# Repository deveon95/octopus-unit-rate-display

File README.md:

# Octopus Unit Rate Display for ESP32

This project gets JSON data from https://octopus.energy

The JSON data is parsed and used to get today's gas and electricity unit rates for the **Tracker** tariff and/or the current **Flexible** prices and/or the current **Agile** prices.

Prices are displayed on two or more 3-digit 7-segment displays to two decimal places if the unit rate is less than 10.00, or one decimal place if the unit rate is greater than or equal to 10.00. Values greater than or equal to 100.00 are displayed with no decimal places.

Negative prices are also supported. In such an event, the first digit will be used for the '-' character.

# Installation

You'll need to install esp-idf to build this project.

```
git clone https://github.com/deveon95/octopus-unit-rate-display
cd esp-idf-json/json-http-client2
chmod 777 getpem.sh
./getpem.sh
idf.py menuconfig
idf.py build flash monitor
```

The getpem.sh script gets the https certificate for octopus.energy. HTTPS is mandatory to use the Octopus API, and this step cannot be skipped! The script does work on Windows as well as Linux; you can run the script with Windows Subsystem for Linux, and you may already be able to run it without installing anything extra if you've installed Git for Windows.

# Configuration
The configuration is opened by running idf.py menuconfig.

You'll need to set the wifi SSID and password so that the ESP32 can connect to the internet, and the tariff codes for the most accurate prices. Note that the latest version of the code has a few extra options for tariff codes not shown in the old screenshots because it has support for more tariffs. The 'ENABLE' options that show up in the latest version of the code should be set to 1 for tariffs that are desired to be displayed or 0 for tariffs to exclude.

To see the console output, set the log verbosity to Info. To disable console output, set to None.

# Console output   
When enabled in the configuration, the console output will show all the unit rates returned by the server, usually for every day of the current month.

# Hardware schematic
See the KiCad design. The board can be mostly assembled by JLCPCB with displays of your choosing added by hand later.

The board and firmware supports up to 8 3-digit 7-segment displays. The lower half of the board can be broken off to give a more compact 4 display version shown in the photo.

For further details of the project, please see [my blog](https://nick-elec.blogspot.com/2023/03/esp32-based-octopus-tracker-unit-rate.html)

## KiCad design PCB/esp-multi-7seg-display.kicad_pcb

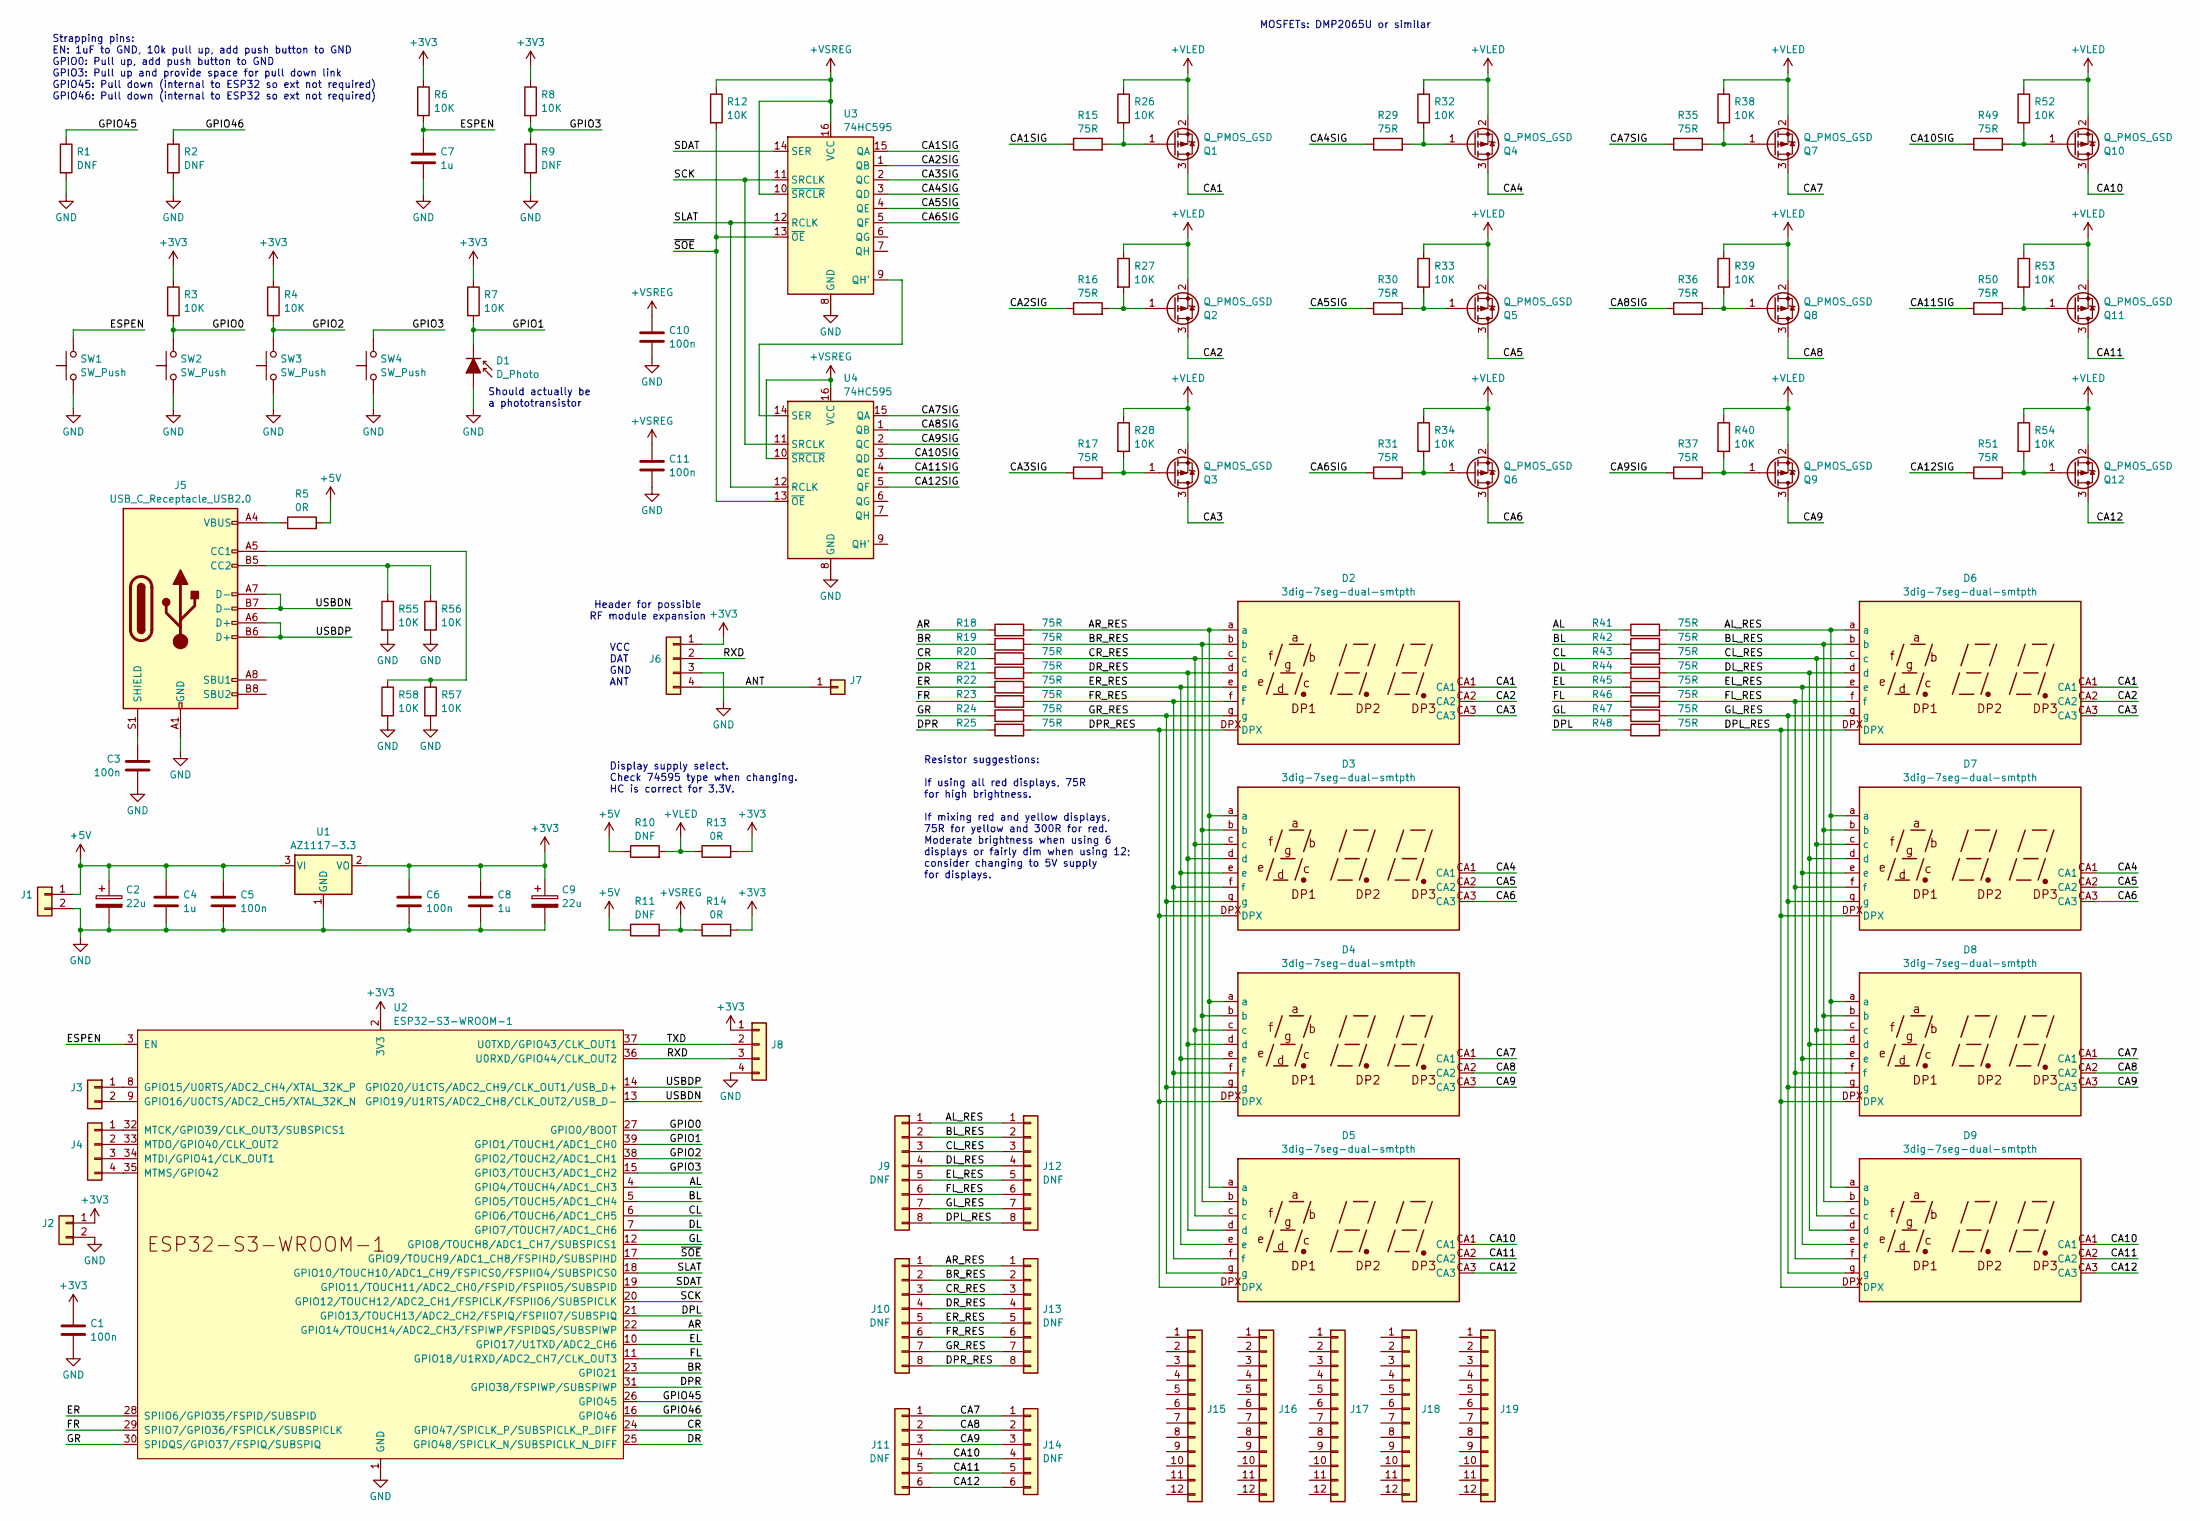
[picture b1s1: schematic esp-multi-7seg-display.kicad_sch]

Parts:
C1, C3, C5, C6, C10, C11: 100n; C_0603_1608Metric_Pad1.08x0.95mm_HandSolder; LCSC Part # C14663
C2, C9: 22u; CP_Elec_6.3x5.4; LCSC Part # C3646800
C4, C7, C8: 1u; C_0603_1608Metric_Pad1.08x0.95mm_HandSolder; LCSC Part # C15849
D1: D_Photo; LED_0805_2012Metric_Pad1.15x1.40mm_HandSolder
D2, D3, D4, D5, D6, D7, D8, D9: 3dig-7seg-dual-smtpth; LCSC Part # C226010
J1, J2, J3: DNF; PinHeader_1x02_P2.54mm_Vertical
J4, J6, J8: DNF; PinHeader_1x04_P2.54mm_Vertical
J5: USB_C_Receptacle_USB2.0; USB_C_Receptacle_G-Switch_GT-USB-7010ASV; LCSC Part # C2988369
J7: DNF; SolderWirePad_1x01_SMD_1x2mm
J9, J10, J12, J13: DNF; PinHeader_2x04_P2.54mm_Vertical_SMD
J11, J14: DNF; PinHeader_2x03_P2.54mm_Vertical_SMD
J15, J16, J17, J18, J19: DNF; PinHeader_1x12_P2.54mm_Vertical
Q1, Q2, Q3, Q4, Q5, Q6, Q7, Q8, Q9, Q10, Q11, Q12: Q_PMOS_GSD; SOT-23; LCSC Part # C10487
R1, R2, R9, R10, R11: DNF; R_0603_1608Metric_Pad0.98x0.95mm_HandSolder
R3, R4, R6, R7, R8, R12, R26, R27, R28, R32, R33, R34, R38, R39, R40, R52, R53, R54, R55, R56, R57, R58: 10K; R_0603_1608Metric_Pad0.98x0.95mm_HandSolder; LCSC Part # C465721
R5, R13, R14: 0R; R_0603_1608Metric_Pad0.98x0.95mm_HandSolder; LCSC Part # C103195
R15, R16, R17, R18, R19, R20, R21, R22, R23, R24, R25, R29, R30, R31, R35, R36, R37, R41, R42, R43, R44, R45, R46, R47, R48, R49, R50, R51: 75R; R_0603_1608Metric_Pad0.98x0.95mm_HandSolder; LCSC Part # C328376
SW1, SW2, SW3, SW4: SW_Push; SW_Push_1P1T_NO_6x6mm_H9.5mm; LCSC Part # C2909692
U1: AZ1117-3.3; SOT-223-3_TabPin2; LCSC Part # C6186
U2: ESP32-S3-WROOM-1; LCSC Part # C2913198
U3, U4: 74HC595; SO-16_5.3x10.2mm_P1.27mm; LCSC Part # C5947

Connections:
+3V3: C1.1, C6.1, C8.1, C9.1, J2.1, J6.1, J8.1, R3.1, R4.1, R6.1, R7.1, R8.1, R13.2, R14.2, U1.2 (VO), U2.2 (3V3)
+5V: C2.1, C4.1, C5.1, J1.1, R5.2, R10.1, R11.1, U1.3 (VI)
+VLED: Q1.2 (S), Q2.2 (S), Q3.2 (S), Q4.2 (S), Q5.2 (S), Q6.2 (S), Q7.2 (S), Q8.2 (S), Q9.2 (S), Q10.2 (S), Q11.2 (S), Q12.2 (S), R10.2, R13.1, R26.1, R27.1, R28.1, R32.1, R33.1, R34.1, R38.1, R39.1, R40.1, R52.1, R53.1, R54.1
+VSREG: C10.1, C11.1, R11.2, R12.1, R14.1, U3.10 (~SRCLR), U3.16 (VCC), U4.10 (~SRCLR), U4.16 (VCC)
/AL: R41.1, U2.4 (GPIO4/TOUCH4/ADC1_CH3)
/AL_RES: D6.a, D7.a, D8.a, D9.a, J9.1, J12.1, R41.2
/ANT: J6.4, J7.1
/AR: R18.1, U2.22 (GPIO14/TOUCH14/ADC2_CH3/FSPIWP/FSPIDQS/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)
/AR_RES: D2.a, D3.a, D4.a, D5.a, J10.1, J13.1, R18.2
/BL: R42.1, U2.5 (GPIO5/TOUCH5/ADC1_CH4)
/BL_RES: D6.b, D7.b, D8.b, D9.b, J9.2, J12.2, R42.2
/BR: R19.1, U2.23 (GPIO21)
/BR_RES: D2.b, D3.b, D4.b, D5.b, J10.2, J13.2, R19.2
/CA1: D2.CA1, D6.CA1, Q1.3 (D)
/CA1SIG: R15.1, U3.15 (QA)
/CA2: D2.CA2, D6.CA2, Q2.3 (D)
/CA2SIG: R16.1, U3.1 (QB)
/CA3: D2.CA3, D6.CA3, Q3.3 (D)
/CA3SIG: R17.1, U3.2 (QC)
/CA4: D3.CA1, D7.CA1, Q4.3 (D)
/CA4SIG: R29.1, U3.3 (QD)
/CA5: D3.CA2, D7.CA2, Q5.3 (D)
/CA5SIG: R30.1, U3.4 (QE)
/CA6: D3.CA3, D7.CA3, Q6.3 (D)
/CA6SIG: R31.1, U3.5 (QF)
/CA7: D4.CA1, D8.CA1, J11.1, J14.1, Q7.3 (D)
/CA7SIG: R35.1, U4.15 (QA)
/CA8: D4.CA2, D8.CA2, J11.2, J14.2, Q8.3 (D)
/CA8SIG: R36.1, U4.1 (QB)
/CA9: D4.CA3, D8.CA3, J11.3, J14.3, Q9.3 (D)
/CA9SIG: R37.1, U4.2 (QC)
/CA10: D5.CA1, D9.CA1, J11.4, J14.4, Q10.3 (D)
/CA10SIG: R49.1, U4.3 (QD)
/CA11: D5.CA2, D9.CA2, J11.5, J14.5, Q11.3 (D)
/CA11SIG: R50.1, U4.4 (QE)
/CA12: D5.CA3, D9.CA3, J11.6, J14.6, Q12.3 (D)
/CA12SIG: R51.1, U4.5 (QF)
/CL: R43.1, U2.6 (GPIO6/TOUCH6/ADC1_CH5)
/CL_RES: D6.c, D7.c, D8.c, D9.c, J9.3, J12.3, R43.2
/CR: R20.1, U2.24 (GPIO47/SPICLK_P/SUBSPICLK_P_DIFF)
/CR_RES: D2.c, D3.c, D4.c, D5.c, J10.3, J13.3, R20.2
/DL: R44.1, U2.7 (GPIO7/TOUCH7/ADC1_CH6)
/DL_RES: D6.d, D7.d, D8.d, D9.d, J9.4, J12.4, R44.2
/DPL: R48.1, U2.21 (GPIO13/TOUCH13/ADC2_CH2/FSPIQ/FSPIIO7/S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)
/DPL_RES: D6.DPX, D7.DPX, D8.DPX, D9.DPX, J9.8, J12.8, R48.2
/DPR: R25.1, U2.31 (GPIO38/FSPIWP/SUBSPIWP)
/DPR_RES: D2.DPX, D3.DPX, D4.DPX, D5.DPX, J10.8, J13.8, R25.2
/DR: R21.1, U2.25 (GPIO48/SPICLK_N/SUBSPICLK_N_DIFF)
/DR_RES: D2.d, D3.d, D4.d, D5.d, J10.4, J13.4, R21.2
/EL: R45.1, U2.10 (GPIO17/U1TXD/ADC2_CH6)
/EL_RES: D6.e, D7.e, D8.e, D9.e, J9.5, J12.5, R45.2
/ER: R22.1, U2.28 (SPIIO6/GPIO35/FSPID/SUBSPID)
/ER_RES: D2.e, D3.e, D4.e, D5.e, J10.5, J13.5, R22.2
/ESPEN: C7.1, R6.2, SW1.2, U2.3 (EN)
/FL: R46.1, U2.11 (GPIO18/U1RXD/ADC2_CH7/CLK_OUT3)
/FL_RES: D6.f, D7.f, D8.f, D9.f, J9.6, J12.6, R46.2
/FR: R23.1, U2.29 (SPIIO7/GPIO36/FSPICLK/SUBSPICLK)
/FR_RES: D2.f, D3.f, D4.f, D5.f, J10.6, J13.6, R23.2
/GL: R47.1, U2.12 (GPIO8/TOUCH8/ADC1_CH7/SUBSPICS1)
/GL_RES: D6.g, D7.g, D8.g, D9.g, J9.7, J12.7, R47.2
/GPIO0: R3.2, SW2.2, U2.27 (GPIO0/BOOT)
/GPIO1: D1.1 (K), R7.2, U2.39 (GPIO1/TOUCH1/ADC1_CH0)
/GPIO2: R4.2, SW3.2, U2.38 (GPIO2/TOUCH2/ADC1_CH1)
/GPIO3: R8.2, R9.1, SW4.2, U2.15 (GPIO3/TOUCH3/ADC1_CH2)
/GPIO45: R1.1, U2.26 (GPIO45)
/GPIO46: R2.1, U2.16 (GPIO46)
/GR: R24.1, U2.30 (SPIDQS/GPIO37/FSPIQ/SUBSPIQ)
/GR_RES: D2.g, D3.g, D4.g, D5.g, J10.7, J13.7, R24.2
/RXD: J6.2, J8.3, U2.36 (U0RXD/GPIO44/CLK_OUT2)
/SCK: U2.20 (GPIO12/TOUCH12/ADC2_CH1/FSPICLK/FSPIIO6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), U3.11 (SRCLK), U4.11 (SRCLK)
/SDAT: U2.19 (GPIO11/TOUCH11/ADC2_CH0/FSPID/FSPIIO5/S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), U3.14 (SER)
/SLAT: U2.18 (GPIO10/TOUCH10/ADC1_CH9/FSPICS0/FSPIIO4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), U3.12 (RCLK), U4.12 (RCLK)
/TXD: J8.2, U2.37 (U0TXD/GPIO43/CLK_OUT1)
/USBDN: J5.A7 (D-), J5.B7 (D-), U2.13 (GPIO19/U1RTS/ADC2_CH8/CLK_OUT2/USB_D-)
/USBDP: J5.A6 (D+), J5.B6 (D+), U2.14 (GPIO20/U1CTS/ADC2_CH9/CLK_OUT1/USB_D+)
/~SOE: R12.2, U2.17 (GPIO9/TOUCH9/ADC1_CH8/FSPIHD/SUBSPIHD), U3.13 (~OE), U4.13 (~OE)
GND: C1.2, C2.2, C3.2, C4.2, C5.2, C6.2, C7.2, C8.2, C9.2, C10.2, C11.2, D1.2 (A), J1.2, J2.2, J5.A1 (GND), J5.A12 (GND), J5.B1 (GND), J5.B12 (GND), J6.3, J8.4, R1.2, R2.2, R9.2, R55.2, R56.2, R57.2, R58.2, SW1.1, SW2.1, SW3.1, SW4.1, U1.1 (GND), U2.1 (GND), U2.40 (GND), U2.41 (GND), U3.8 (GND), U4.8 (GND)
unnamed: J3.1, U2.8 (GPIO15/U0RTS/ADC2_CH4/XTAL_32K_P)
unnamed: J3.2, U2.9 (GPIO16/U0CTS/ADC2_CH5/XTAL_32K_N)
unnamed: J4.1, U2.32 (MTCK/GPIO39/CLK_OUT3/SUBSPICS1)
unnamed: J4.2, U2.33 (MTDO/GPIO40/CLK_OUT2)
unnamed: J4.3, U2.34 (MTDI/GPIO41/CLK_OUT1)
unnamed: J4.4, U2.35 (MTMS/GPIO42)
unnamed: J5.A5 (CC1), R57.1, R58.1
unnamed: J5.B5 (CC2), R55.1, R56.1
unnamed: C3.1, J5.S1 (SHIELD)
unnamed: J5.A4 (VBUS), J5.A9 (VBUS), J5.B4 (VBUS), J5.B9 (VBUS), R5.1
unnamed: Q1.1 (G), R15.2, R26.2
unnamed: Q2.1 (G), R16.2, R27.2
unnamed: Q3.1 (G), R17.2, R28.2
unnamed: Q4.1 (G), R29.2, R32.2
unnamed: Q5.1 (G), R30.2, R33.2
unnamed: Q6.1 (G), R31.2, R34.2
unnamed: Q7.1 (G), R35.2, R38.2
unnamed: Q8.1 (G), R36.2, R39.2
unnamed: Q9.1 (G), R37.2, R40.2
unnamed: Q10.1 (G), R49.2, R52.2
unnamed: Q11.1 (G), R50.2, R53.2
unnamed: Q12.1 (G), R51.2, R54.2
unnamed: U3.9 (QH'), U4.14 (SER)

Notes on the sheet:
VCC DAT GND ANT
MOSFETs: DMP2065U or similar
Resistor suggestions: If using all red displays, 75R for high brightness. If mixing red and yellow displays, 75R for yellow and 300R for red. Moderate brightness when using 6 displays or fairly dim when using 12; consider changing to 5V supply for displays.
Header for possible RF module expansion
Should actually be a phototransistor
Strapping pins: EN: 1uF to GND, 10k pull up, add push button to GND GPIO0: Pull up, add push button to GND GPIO3: Pull up and provide space for pull down link GPIO45: Pull down (internal to ESP32 so ext not required) GPIO46: Pull down (internal to ESP32 so ext not required)
Display supply select. Check 74595 type when changing. HC is correct for 3.3V.

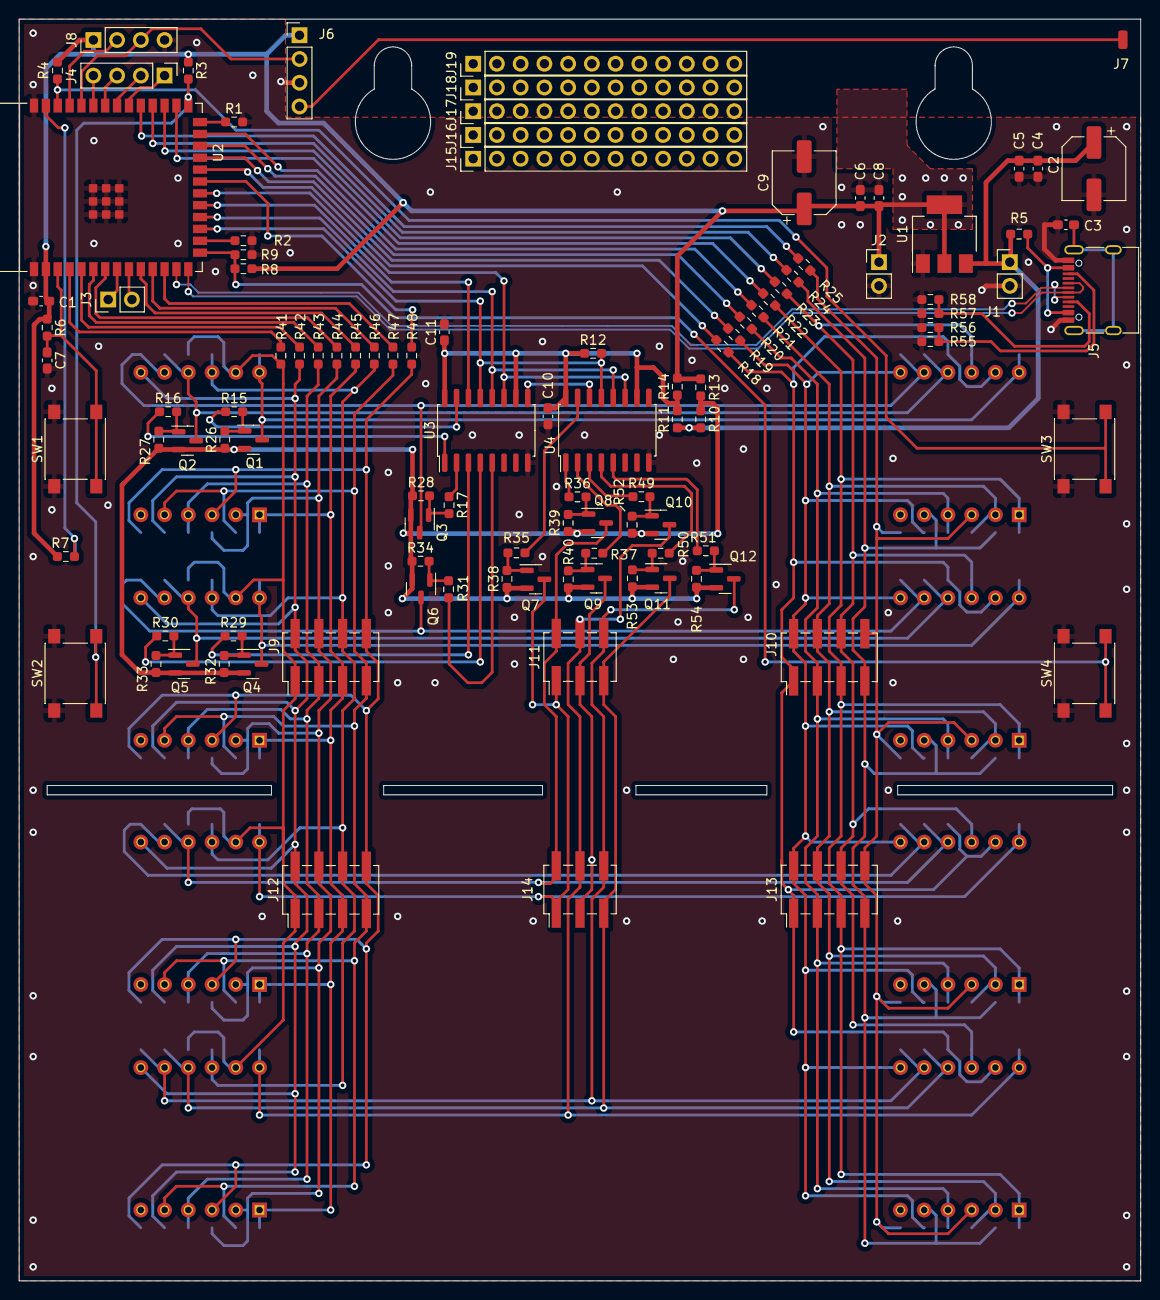
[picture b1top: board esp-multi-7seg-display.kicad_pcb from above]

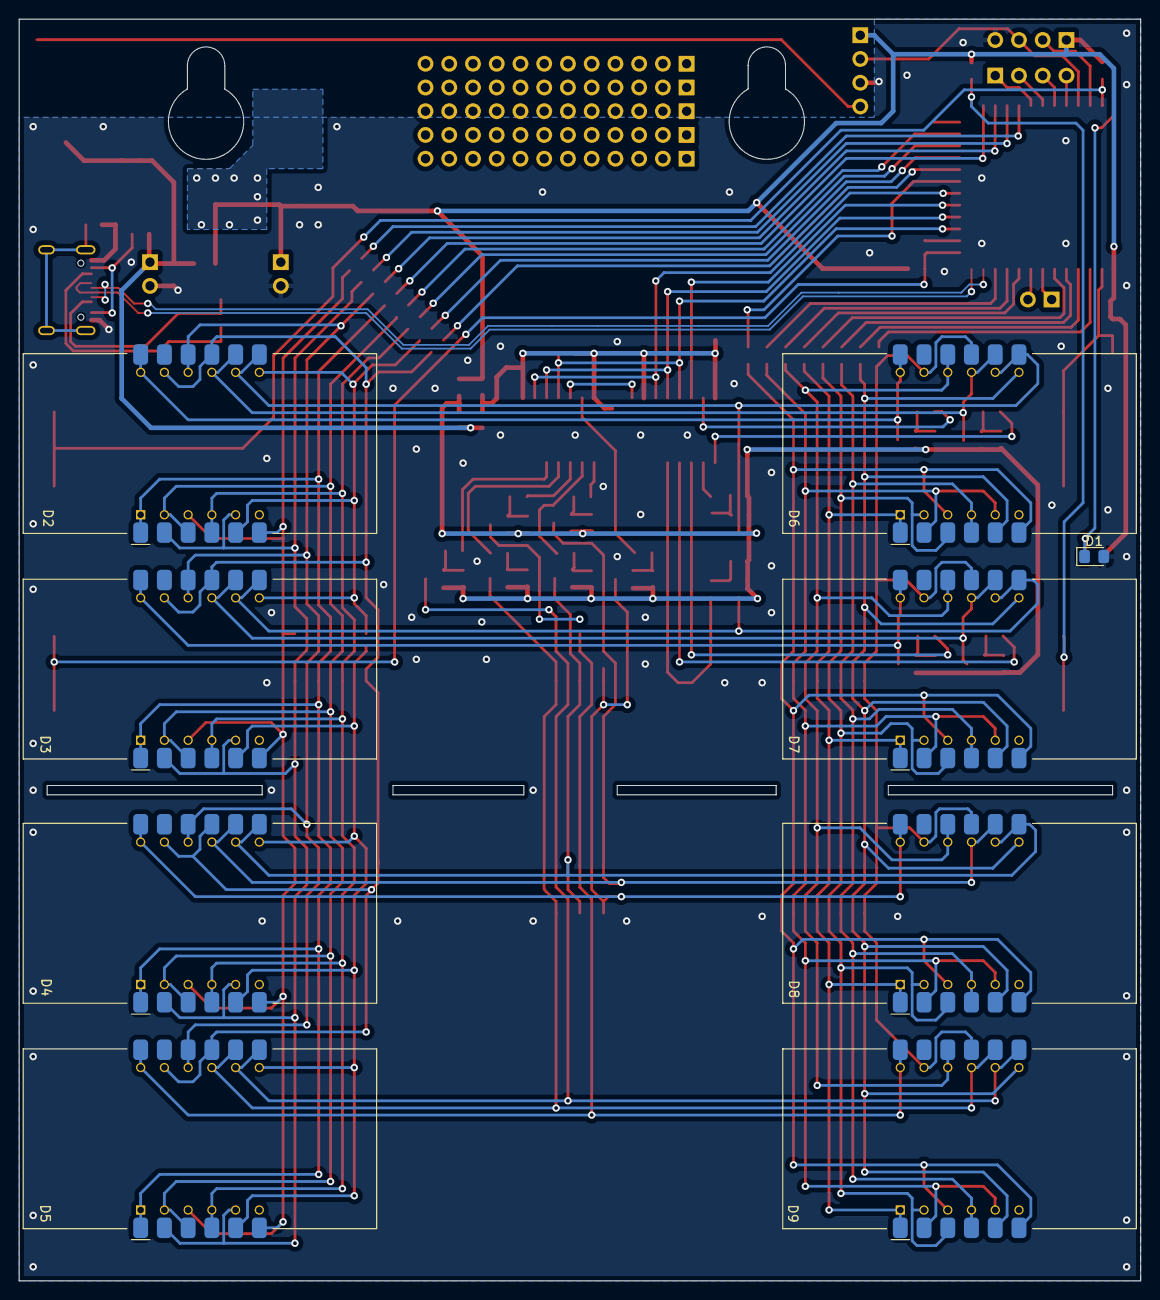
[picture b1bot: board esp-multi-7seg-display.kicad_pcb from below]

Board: 2 copper layers, 120.0 x 135.0 mm, 117 parts (9 on the bottom side), 100 nets.

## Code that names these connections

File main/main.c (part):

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#define pin_segGL 8
#define pin_segDPL 13

#define pin_SOE 9
#define pin_SLAT 10
#define pin_SDAT 11
#define pin_SCK 12

#define pin_BUTTON2 0
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#define ADC_FILTER_LENGTH 30
#define ADC_MAX_VALUE 4095
#define ADC_HYSTERESIS 200
static const adc_channel_t channel = ADC_CHANNEL_0;     //GPIO1 for ADC1
static const adc_bits_width_t width = ADC_WIDTH_BIT_12;
static const adc_atten_t atten = ADC_ATTEN_DB_11;
//static const adc_unit_t unit = ADC_UNIT_1;
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    
    // Turn off all digits
    // SPI code needed here
    gpio_set_level(pin_SOE, 1);
    
    // Turn off all segments by setting specified bits high in 'Write 1 to set' register
    GPIO.out_w1ts =      ((uint32_t)1 << pin_segAL)
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        // SPI code needed here
        for (uint8_t i = 0; i < NUM_OF_ANODES; i++)
        {
            gpio_set_level(pin_SDAT, (NUM_OF_ANODES - 1 - current_disp_index) == i ? 0 : 1);
            ets_delay_us(SR_DELAY_US);
            gpio_set_level(pin_SCK, 1);
            ets_delay_us(SR_DELAY_US);
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        }
        
        ets_delay_us(SR_DELAY_US);
        gpio_set_level(pin_SLAT, 1);
        ets_delay_us(SR_DELAY_US);
        gpio_set_level(pin_SLAT, 0);
        ets_delay_us(SR_DELAY_US);
        gpio_set_level(pin_SOE, 0);
        
        // Turn on required segments
        GPIO.out_w1tc =
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                         | ((uint64_t)1 << pin_segFR)
                         | ((uint64_t)1 << pin_segGR)
                         | ((uint64_t)1 << pin_segDPR)
                         | ((uint64_t)1 << pin_SLAT)
                         | ((uint64_t)1 << pin_SOE)
                         | ((uint64_t)1 << pin_SDAT)
                         | ((uint64_t)1 << pin_SCK);
    io_conf.pull_down_en = GPIO_PULLDOWN_DISABLE;
    io_conf.pull_up_en = GPIO_PULLUP_DISABLE;
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    /*
    spi_bus_config_t buscfg={
        .miso_io_num = -1,
        .mosi_io_num = pin_SDAT,
        .sclk_io_num = pin_SCK,
        .quadwp_io_num = -1,
        .quadhd_io_num = -1,
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        .cs_ena_pretrans=2,
        .cs_ena_posttrans=2,
        .clock_speed_hz=1000000,
        .spics_io_num=pin_SLAT,
    }
    ret = spi_bus_add_device(SPi2_HOST, &devcfg, &spihandle);
    ESP_ERROR_CHECK(ret);
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
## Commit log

2023-03-05 Move relevant example to the top level folder and remove all the other examples
2023-03-05 Added octopus-unit-rate-display project files
2023-10-14 Implemented shift registers for PCB version. Added flexible tariff price for comparison.
2023-12-22 Added agile tariff
2023-12-22 Switched tracker API to latest API. *Warning: credentials are present in sdkconfig file, should be excluded from repo*
2023-12-23 Added display of tomorrow's tracker price, switched day calculation to use epoch time so that tracker should behave as expected during DST under new API
2023-12-23 Add valid_from checking to flexible tariff display because first result can be for the next period which is yet to begin, and remove some unnecessary log messages
2023-12-23 Clean up decimal point code
2023-12-27 Implemented dynamic re-fetching system
2023-12-27 Tomorrow displays now show third dash when today's prices have been obtained
2024-01-30 Added ability to disable display of tomorrow's prices and instead show flexible or tracker alongside today's price
2024-01-30 Update README.md
    Added message about old API
2024-02-18 various changes for esp-idf 5.2
2025-01-05 Add PCB
2025-01-05 Update README.md to reflect addition of PCB design.

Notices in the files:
main/main.c:
Copyright (c) 2023 Nick Schollar
Licenced under MIT Licence
PCB/esp-multi-7seg-display.kicad_pcb:
© 2023 Nick Schollar
